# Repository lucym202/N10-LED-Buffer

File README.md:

# N10 LED Buffer

A small LED buffer add‑on for the Stormforge N10 (Chinese mATX NAS chassis) SAS backplane. It buffers the ACT (activity) signals so higher-current LEDs can be used while keeping the board's activity indicators functional.

## Images
See repository images for an example installation.

## Quick summary
- Cut the trace from the activity LED cathode to P11.
- Connect the ACT pads to the P11 pins on the SAS connectors.
- Connect the LED pads to the activity LED cathodes.
- Solder and secure; test before final mounting.
- You could redesign the board if you have trouble soldering 0603 components, but keep in mind the backplane uses 0603 resistors and LEDs

## Required tools & parts
- Fine soldering iron - 2mm chisel tip, 0.7 mm solder wire, or smaller
- Flux, solder wick, fine tweezers (ESD safe)
- Thin insulated wire (30 SWG/28 AWG Kynar)
- Hobby knife or micro rotary tool for cutting PCB traces
- Magnification (I used a 100× microscope)
- Isopropyl alcohol and brush for cleaning
- Foam tape, to secure buffer board to backplane board
- 5x 2K Resistor SMD 0603
- 5x 12K Resistor SMD 0603
- 1x 470R Resistor SMD 0603
- 5x BC847B Transistor SMD SOT-23
- 1x 3.3v Zener Diode SMD 1206
- For testing, 5x red LED and 5x ~1K6 resistor, through-hole
- SATA host interface for testing - I used an old laptop with an eSATA port, and an eSATA to SATA cable
- Any working SATA hard drive for testing - sacrificial

## Bench testing the PCB (before attaching to backplane)
Perform a quick bench test to verify the buffer PCB is working before you solder it into the backplane.

1. For each channel, connect one LED with a 1.6 kΩ series resistor between the board 5V pad and the corresponding LED pad (one LED + resistor per channel). This provides a visible load for each output.
2. Attach the multimeter negative (COM) probe to GND on the board.
3. Apply +5V to the board by connecting +5V between the board 5V pad and GND.
4. All LEDs should be off with no ACT input asserted.

Measurements you should see (example values from the builder):
- D1 cathode voltage: should be < 3.3 V (builder saw ~2.2 V).
- ACT pad voltages (with no input): should be < 3.3 V (builder saw ~0.6 V).
- ACT pad currents (with no input): should be < 300 µA (builder saw ~220 µA).

Verification step (per-channel):
- To confirm a channel responds, briefly touch the ACT pad with the multimeter + probe while the meter is set to measure current, or connect the pad to ground; the corresponding LED should light.

Notes:
- These checks verify the buffer's idle voltages and the small leakage/source currents seen on the ACT inputs. If values are significantly outside the ranges above, re-check soldering, component orientation, and that there are no accidental shorts.

## Installation (short)
1. Power down and remove the backplane for access.
2. Locate and cut 5x copper traces between the activity LED cathode and P11; verify isolation with a multimeter.
3. For each channel, solder a thin wire from the backplane P11 pad to the buffer board ACT pad.
4. For each channel, solder a thin wire from the buffer board LED pad to the isolated LED cathode pad.
5. Connect the GND pad to any ground point on the backplane. This can be taken from the ground plane near the buffer board, scrape the solder mask off with a tool to create a solder pad
6. Connect the 5V pad to the 5V rail on the backplane. This can be taken from the positive side of any of the second row of electrolytic capacitors. Power up the backplane with a test power supply and verify with a multimeter.
7. Check continuity, verify no shorts, and bench test LED activity with a sacrificial SATA hard drive on all ports. You will need a SATA interface plugged into the back of the board on the corresponding channel to observe activity
8. Secure wiring with Kapton tape or super glue for strain relief, particularly on front side of the PCB.
9. Reinstall and test

## Hand-soldering 0603 SMD (brief)
These instructions assume you are right-handed or prefer soldering with your right hand, flip these directions if you prefer soldering with your left hand
- Use strong magnification (100× if available), plenty of flux, and a fine-tip iron.
- Turn the board so the ACT pads face right. Apply flux and tin one pad for each component on ACT side of the board.
- Start with the resistors, then the transistors, and finally the diode. Work from left to right
- Hold the component flat to the board with the tweezers in your left hand, and your soldering iron in your right
- Reflow the pad with the soldering iron, then move the component into place and allow the solder to cool
- Once all components of each type are in place, turn the board so the ACT pads face left, and solder the opposite pad(s) with a minimal amount of solder, then reflow the tacked pad if needed.
- Clean flux with isopropyl alcohol. Use solder wick to remove bridges.

## Testing & troubleshooting
- If LED is off: check polarity, continuity, and solder joints.
- If LED is on when no drive is installed: Disconnect the wire from the ACT pad. If LED turns off, check for solder bridges on the SAS connector. If LED remains on, check transistor voltages, replace transistor if defective
- If channel behaves incorrectly: ensure the original trace was fully cut and the ACT wiring is solid.
- If LED stays on only when drive is installed: verify your drive configuration, many SAS drives hold the indicator on from spin-up and blink off for activity

## Safety & notes
- This mod changes the backplane; proceed at your own risk. Use ESD precautions.
- Use a current limited power supply for testing, the entire board should draw <30mA
- Builder note: 100× microscope made assembly far easier for 0603 parts.

## License
Licensed under the CERN Open Hardware Licence v2 - Strongly Reciprocal (CERN-OHL-S-2.0). See the LICENSE file for details.

SPDX-License-Identifier: CERN-OHL-S-2.0

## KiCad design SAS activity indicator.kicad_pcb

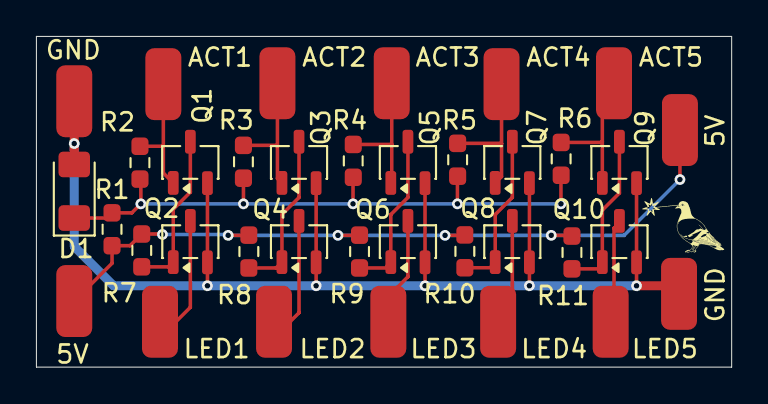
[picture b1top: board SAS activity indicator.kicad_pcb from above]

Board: 2 copper layers, 38.6 x 18.4 mm, 36 parts (0 on the bottom side), 18 nets.

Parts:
5V, 5V#2: +5V; SolderWirePad_1x01_SMD_2x4mm
ACT1: SAS_ACT1; SolderWirePad_1x01_SMD_2x4mm
ACT2: SAS_ACT2; SolderWirePad_1x01_SMD_2x4mm
ACT3: SAS_ACT3; SolderWirePad_1x01_SMD_2x4mm
ACT4: SAS_ACT4; SolderWirePad_1x01_SMD_2x4mm
ACT5: SAS_ACT5; SolderWirePad_1x01_SMD_2x4mm
D1: 3.3V; D_1206_3216Metric_Pad1.42x1.75mm_HandSolder
GND: GND; SolderWirePad_1x01_SMD_2x4mm
GND#2: GND; SolderWirePad_1x01_SMD_2x4mm
LED1: LED1; SolderWirePad_1x01_SMD_2x4mm
LED2: LED2; SolderWirePad_1x01_SMD_2x4mm
LED3: LED3; SolderWirePad_1x01_SMD_2x4mm
LED4: LED4; SolderWirePad_1x01_SMD_2x4mm
LED5: LED5; SolderWirePad_1x01_SMD_2x4mm
Q1, Q2, Q3, Q4, Q5, Q6, Q7, Q8, Q9, Q10: BC847B; SOT-23-3-CESWAP
R1: 470; R_0603_1608Metric_Pad0.98x0.95mm_HandSolder
R2, R3, R4, R5, R6: 12K; R_0603_1608Metric_Pad0.98x0.95mm_HandSolder
R7, R8, R9, R10, R11: 10K; R_0603_1608Metric_Pad0.98x0.95mm_HandSolder

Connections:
+3V3: D1.1 (K), R1.2, R2.2, R3.2, R4.2, R5.2, R6.2
+5V: 5V.1, 5V#2.1, R1.1, R7.1, R8.1, R9.1, R10.1, R11.1
GND: D1.2 (A), GND.1, GND#2.1, Q1.3 (E), Q2.3 (E), Q3.3 (E), Q4.3 (E), Q5.3 (E), Q6.3 (E), Q7.3 (E), Q8.3 (E), Q9.3 (E), Q10.3 (E)
unnamed: ACT1.1, Q1.1 (B), R2.1
unnamed: ACT2.1, Q3.1 (B), R3.1
unnamed: ACT3.1, Q5.1 (B), R4.1
unnamed: ACT4.1, Q7.1 (B), R5.1
unnamed: ACT5.1, Q9.1 (B), R6.1
unnamed: LED1.1, Q2.2 (C)
unnamed: LED2.1, Q4.2 (C)
unnamed: LED3.1, Q6.2 (C)
unnamed: LED4.1, Q8.2 (C)
unnamed: LED5.1, Q10.2 (C)
unnamed: Q1.2 (C), Q2.1 (B), R7.2
unnamed: Q3.2 (C), Q4.1 (B), R8.2
unnamed: Q5.2 (C), Q6.1 (B), R9.2
unnamed: Q7.2 (C), Q8.1 (B), R10.2
unnamed: Q9.2 (C), Q10.1 (B), R11.2
